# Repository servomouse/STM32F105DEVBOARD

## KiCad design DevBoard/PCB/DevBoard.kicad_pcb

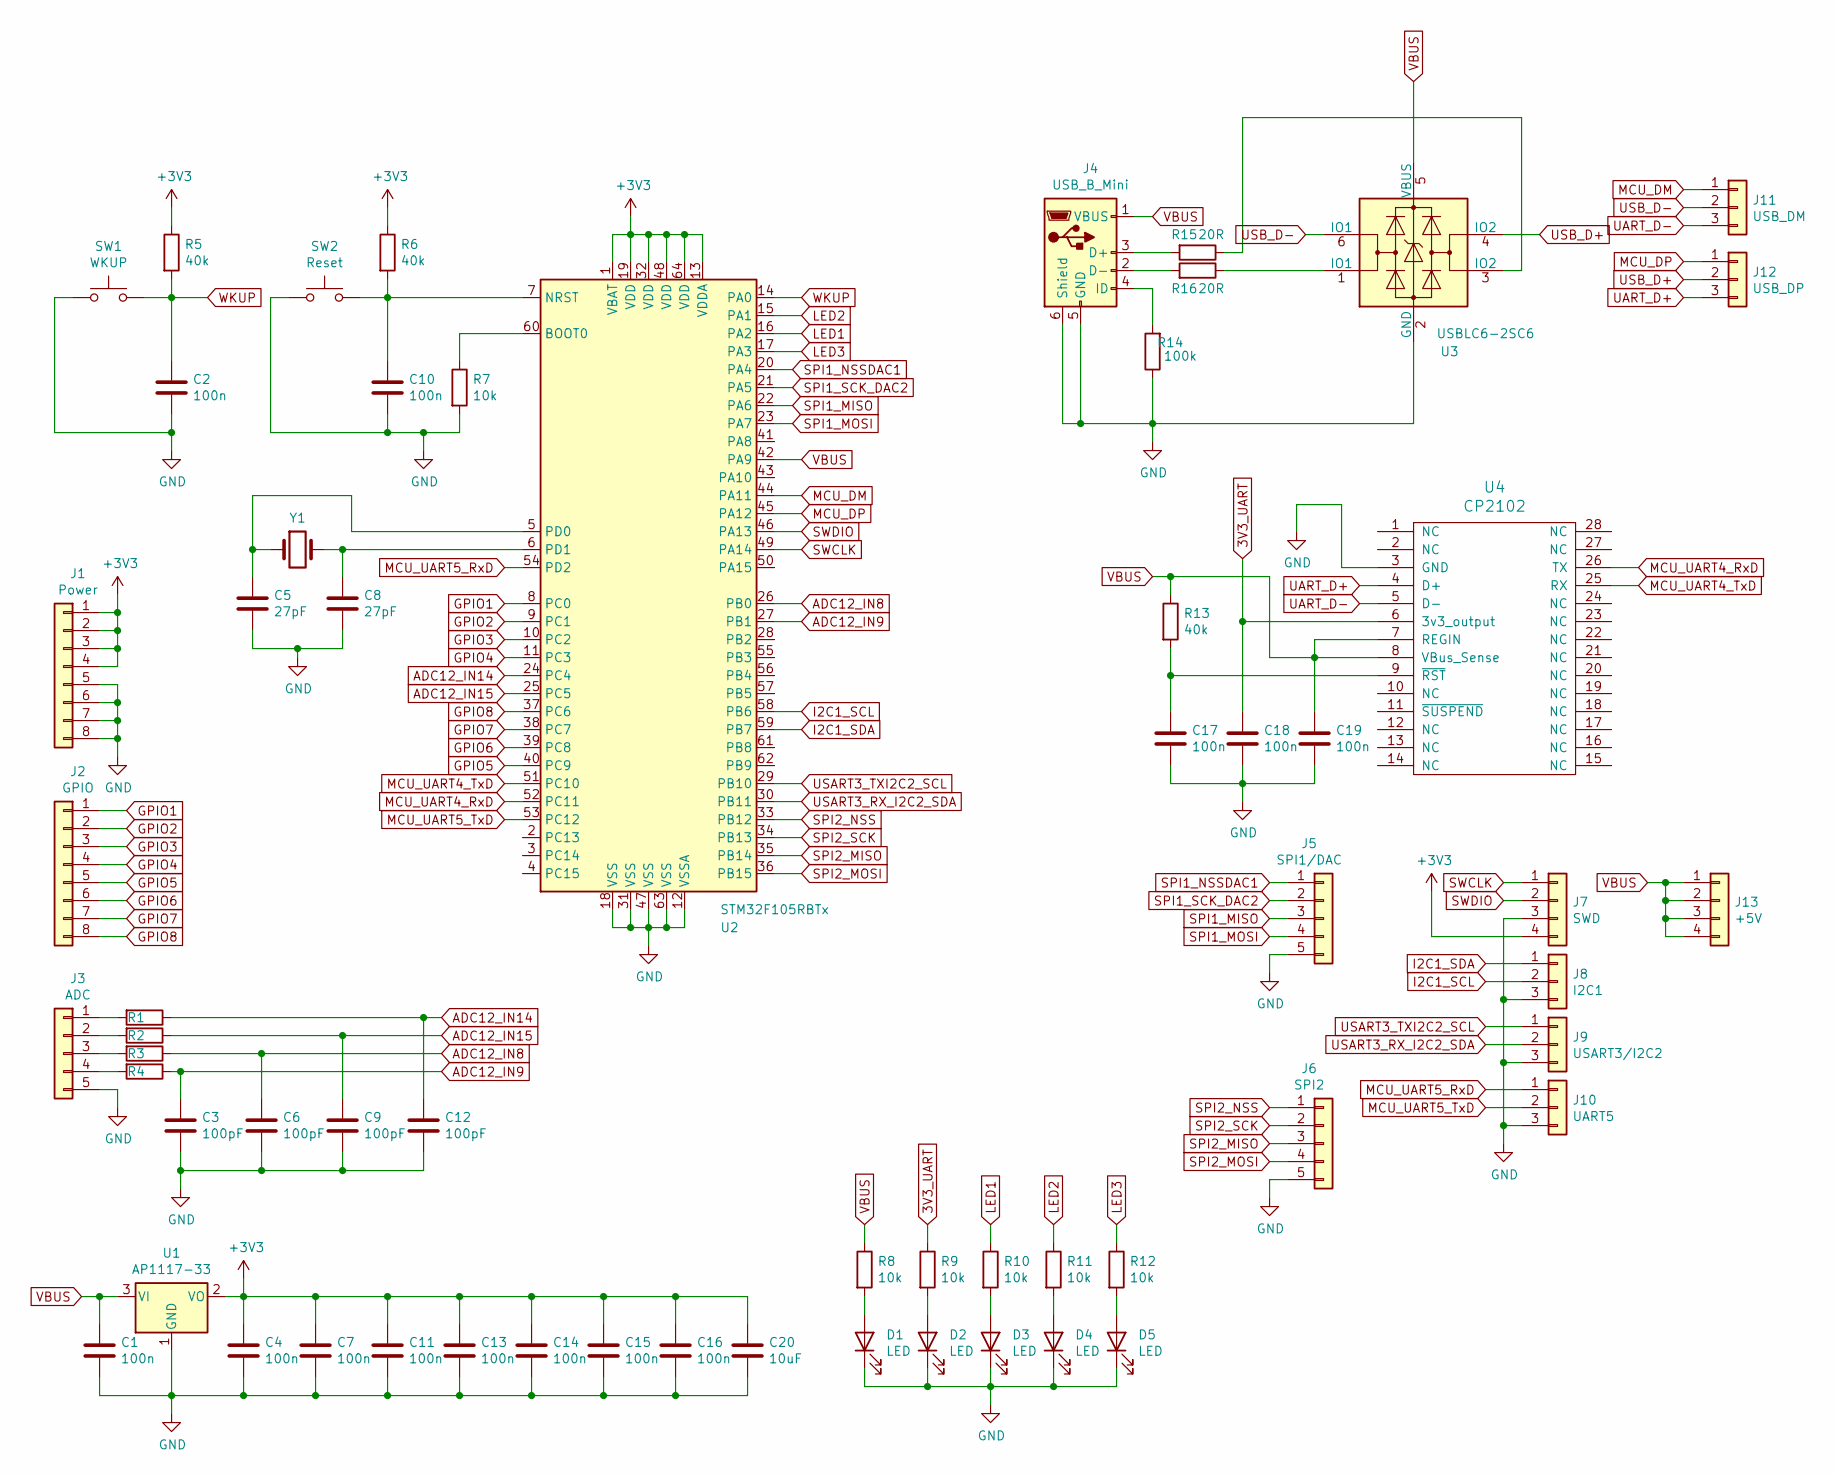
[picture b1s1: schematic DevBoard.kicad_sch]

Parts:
C1, C2, C4, C7, C10, C11, C13, C14, C15, C16, C17, C18, C19: 100n; 0402
C3, C6, C9, C12: 100pF; 0402
C5, C8: 27pF; 0402
C20: 10uF; CP_EIA-6032-15_Kemet-U
D1, D2, D3, D4, D5: LED; LED_0603
J1: Power; Conn_01x08_2.54mm_Straight
J2: GPIO; Conn_01x08_2.54mm_Straight
J3: ADC; Conn_01x05_2.54mm_Straight
J4: USB_B_Mini; USB_Mini-B_Lumberg_2486_01_Horizontal
J5: SPI1/DAC; Conn_01x05_2.54mm_Straight
J6: SPI2; Conn_01x05_2.54mm_Straight
J7: SWD; Conn_01x04_2.54mm_Straight
J8: I2C1; Conn_01x03_2.54mm_Straight
J9: USART3/I2C2; Conn_01x03_2.54mm_Straight
J10: UART5; Conn_01x03_2.54mm_Straight
J11: USB_DM; Conn_01x03_2.54mm_Straight
J12: USB_DP; Conn_01x03_2.54mm_Straight
J13: +5V; Conn_01x04_2.54mm_Straight
R1, R2, R3, R4, R14: 100k; 0420
R5, R6, R13: 40k; 0420
R7, R8, R9, R10, R11, R12: 10k; 0420
R15, R16: 20R; 0603
SW1: WKUP; SW_PUSH_6mm_H4.3mm
SW2: Reset; SW_PUSH_6mm_H4.3mm
U1: AP1117-33; SOT-223-3_TabPin2
U2: STM32F105RBTx; LQFP-64_10x10mm_P0.5mm
U3: USBLC6-2SC6; SOT-23-6
U4: CP2102; QFN-28-1EP_5x5mm_P0.5mm_EP3.35x3.35mm
Y1: Crystal; HC-49SM

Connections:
3V3_UART: C18.1, R9.1, U4.6 (3v3_output)
+3V3: C4.1, C7.1, C11.1, C13.1, C14.1, C15.1, C16.1, C20.1, J1.1, J1.2, J1.3, J1.4, J7.4, R5.1, R6.1, U1.2 (VO), U2.1 (VBAT), U2.13 (VDDA), U2.19 (VDD), U2.32 (VDD), U2.48 (VDD), U2.64 (VDD)
ADC12_IN8: C6.1, R3.1, U2.26 (PB0)
ADC12_IN9: C3.1, R4.1, U2.27 (PB1)
ADC12_IN14: C12.1, R1.1, U2.24 (PC4)
ADC12_IN15: C9.1, R2.1, U2.25 (PC5)
GND: C1.2, C2.2, C3.2, C4.2, C5.2, C6.2, C7.2, C8.2, C9.2, C10.2, C11.2, C12.2, C13.2, C14.2, C15.2, C16.2, C17.2, C18.2, C19.2, C20.2, D1.1 (K), D2.1 (K), D3.1 (K), D4.1 (K), D5.1 (K), J1.5, J1.6, J1.7, J1.8, J3.5, J4.5 (GND), J4.6 (Shield), J5.5, J6.5, J7.3, J8.3, J9.3, J10.3, R7.2, R14.1, SW1.1, SW2.1, U1.1 (GND), U2.12 (VSSA), U2.18 (VSS), U2.31 (VSS), U2.47 (VSS), U2.63 (VSS), U3.2 (GND), U4.3 (GND)
GPIO1: J2.1, U2.8 (PC0)
GPIO2: J2.2, U2.9 (PC1)
GPIO3: J2.3, U2.10 (PC2)
GPIO4: J2.4, U2.11 (PC3)
GPIO5: J2.5, U2.40 (PC9)
GPIO6: J2.6, U2.39 (PC8)
GPIO7: J2.7, U2.38 (PC7)
GPIO8: J2.8, U2.37 (PC6)
I2C1_SCL: J8.2, U2.58 (PB6)
I2C1_SDA: J8.1, U2.59 (PB7)
LED1: R10.1, U2.16 (PA2)
LED2: R11.1, U2.15 (PA1)
LED3: R12.1, U2.17 (PA3)
MCU_DM: J11.1, U2.44 (PA11)
MCU_DP: J12.1, U2.45 (PA12)
MCU_UART4_RxD: U2.52 (PC11), U4.26 (TX)
MCU_UART4_TxD: U2.51 (PC10), U4.25 (RX)
MCU_UART5_RxD: J10.1, U2.54 (PD2)
MCU_UART5_TxD: J10.2, U2.53 (PC12)
unnamed: C5.1, U2.5 (PD0), Y1.1
unnamed: C8.1, U2.6 (PD1), Y1.2
unnamed: C10.1, R6.2, SW2.2, U2.7 (NRST)
unnamed: C17.1, R13.2, U4.9 (~RST)
unnamed: D1.2 (A), R8.2
unnamed: D2.2 (A), R9.2
unnamed: D3.2 (A), R10.2
unnamed: D4.2 (A), R11.2
unnamed: D5.2 (A), R12.2
unnamed: J3.1, R1.2
unnamed: J3.2, R2.2
unnamed: J3.3, R3.2
unnamed: J3.4, R4.2
unnamed: J4.2 (D-), R16.2
unnamed: J4.3 (D+), R15.2
unnamed: J4.4 (ID), R14.2
unnamed: R7.1, U2.60 (BOOT0)
unnamed: R15.1, U3.3 (IO2)
unnamed: R16.1, U3.1 (IO1)
SPI1_MISO: J5.3, U2.22 (PA6)
SPI1_MOSI: J5.4, U2.23 (PA7)
SPI1_NSSDAC1: J5.1, U2.20 (PA4)
SPI1_SCK_DAC2: J5.2, U2.21 (PA5)
SPI2_MISO: J6.3, U2.35 (PB14)
SPI2_MOSI: J6.4, U2.36 (PB15)
SPI2_NSS: J6.1, U2.33 (PB12)
SPI2_SCK: J6.2, U2.34 (PB13)
SWCLK: J7.1, U2.49 (PA14)
SWDIO: J7.2, U2.46 (PA13)
UART_D+: J12.3, U4.4 (D+)
UART_D-: J11.3, U4.5 (D-)
USART3_RX_I2C2_SDA: J9.2, U2.30 (PB11)
USART3_TXI2C2_SCL: J9.1, U2.29 (PB10)
USB_D+: J12.2, U3.4 (IO2)
USB_D-: J11.2, U3.6 (IO1)
VBUS: C1.1, C19.1, J4.1 (VBUS), J13.1, J13.2, J13.3, J13.4, R8.1, R13.1, U1.3 (VI), U2.42 (PA9), U3.5 (VBUS), U4.7 (REGIN), U4.8 (VBus_Sense)
WKUP: C2.1, R5.2, SW1.2, U2.14 (PA0)

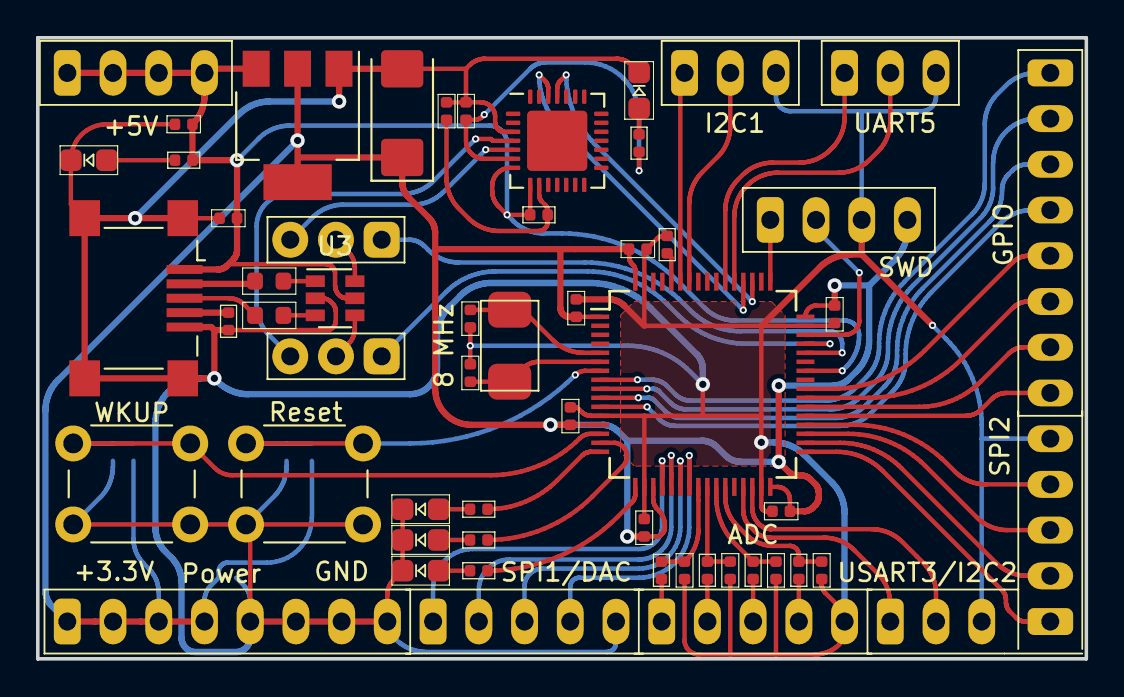
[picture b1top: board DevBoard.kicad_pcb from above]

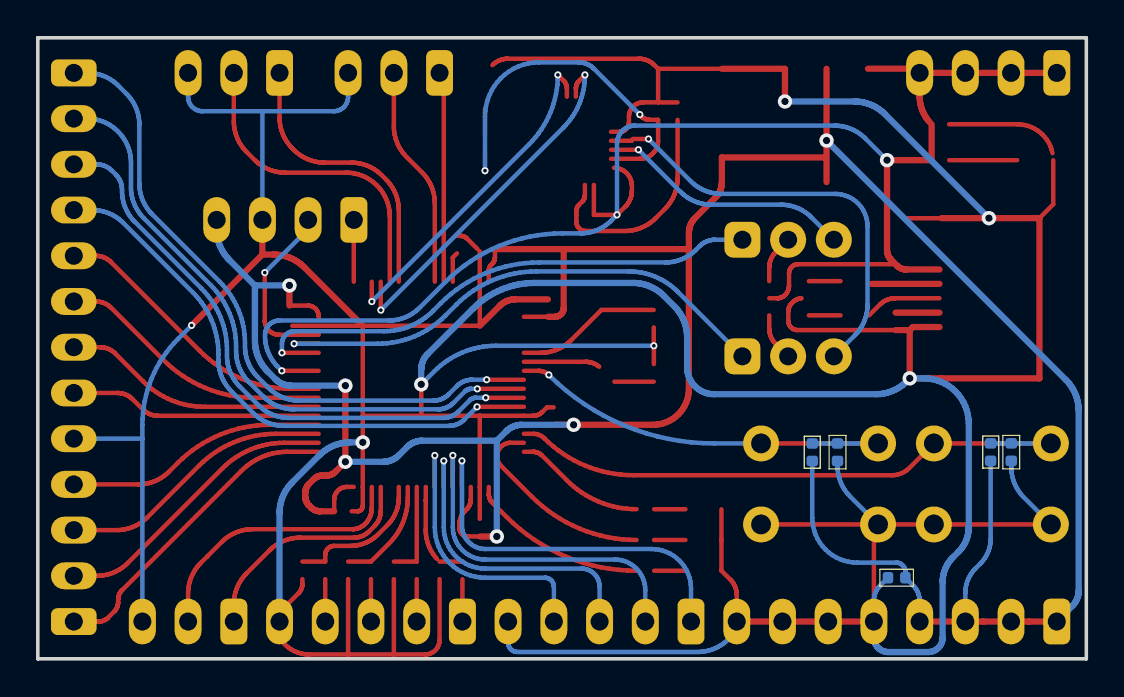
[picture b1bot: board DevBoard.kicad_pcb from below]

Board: 2 copper layers, 58.2 x 34.5 mm, 61 parts (5 on the bottom side), 63 nets.

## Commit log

2020-12-02 Final version of pcb
2020-12-02 Мелкие правки
